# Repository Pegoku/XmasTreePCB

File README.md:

# XmasTreePCB

## Overview
This is a simple and customizable RGB Xmas tree.

## Features
- [x] **ESP32 Controlled**: Easy to program MCU.
- [x] **Neopixels**: Easy to use RGB LEDs.

## Media
<details>
    <summary>Images</summary>

)
</details>

<details>
    <summary>Video</summary>

</details>

## Contributing
Contributions are welcome! Please fork the repository and submit a pull request with your changes.

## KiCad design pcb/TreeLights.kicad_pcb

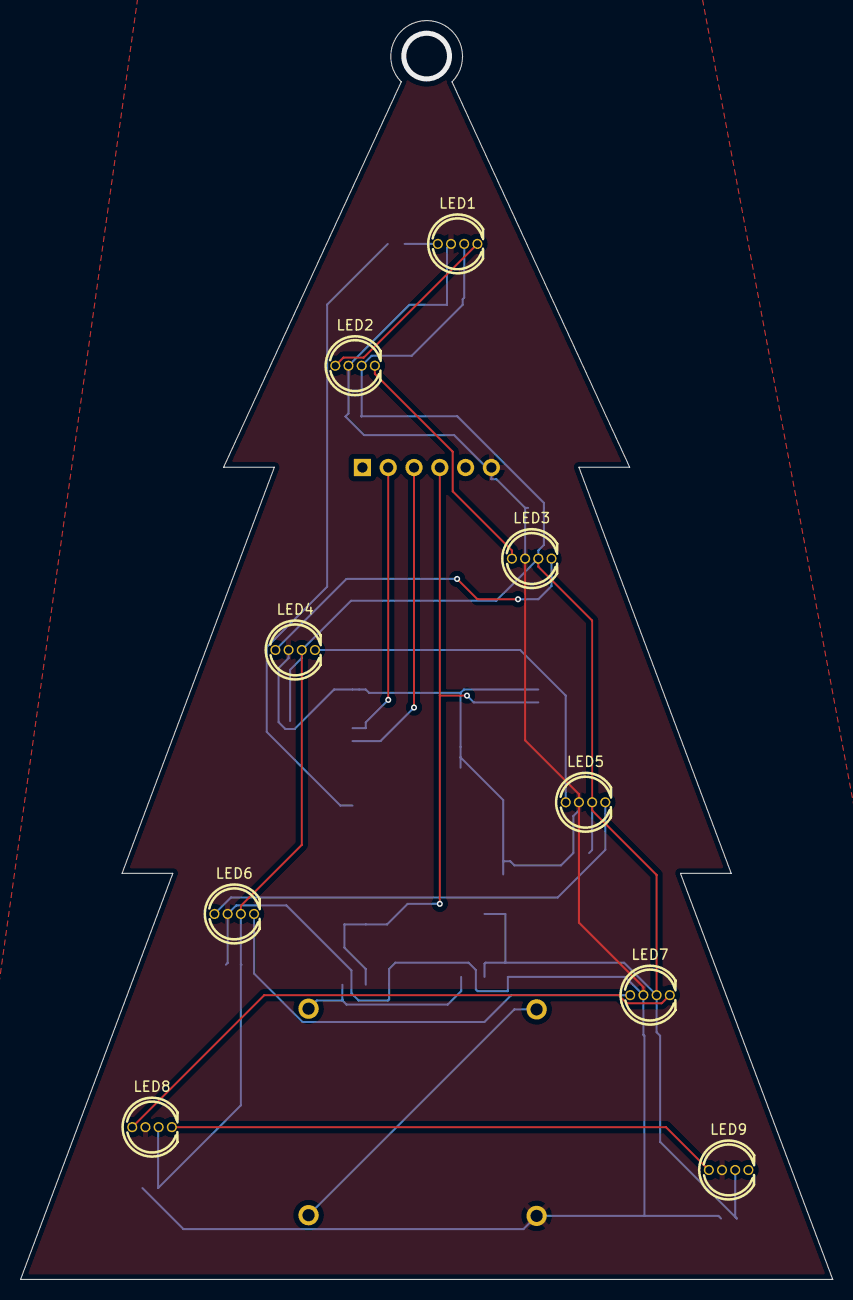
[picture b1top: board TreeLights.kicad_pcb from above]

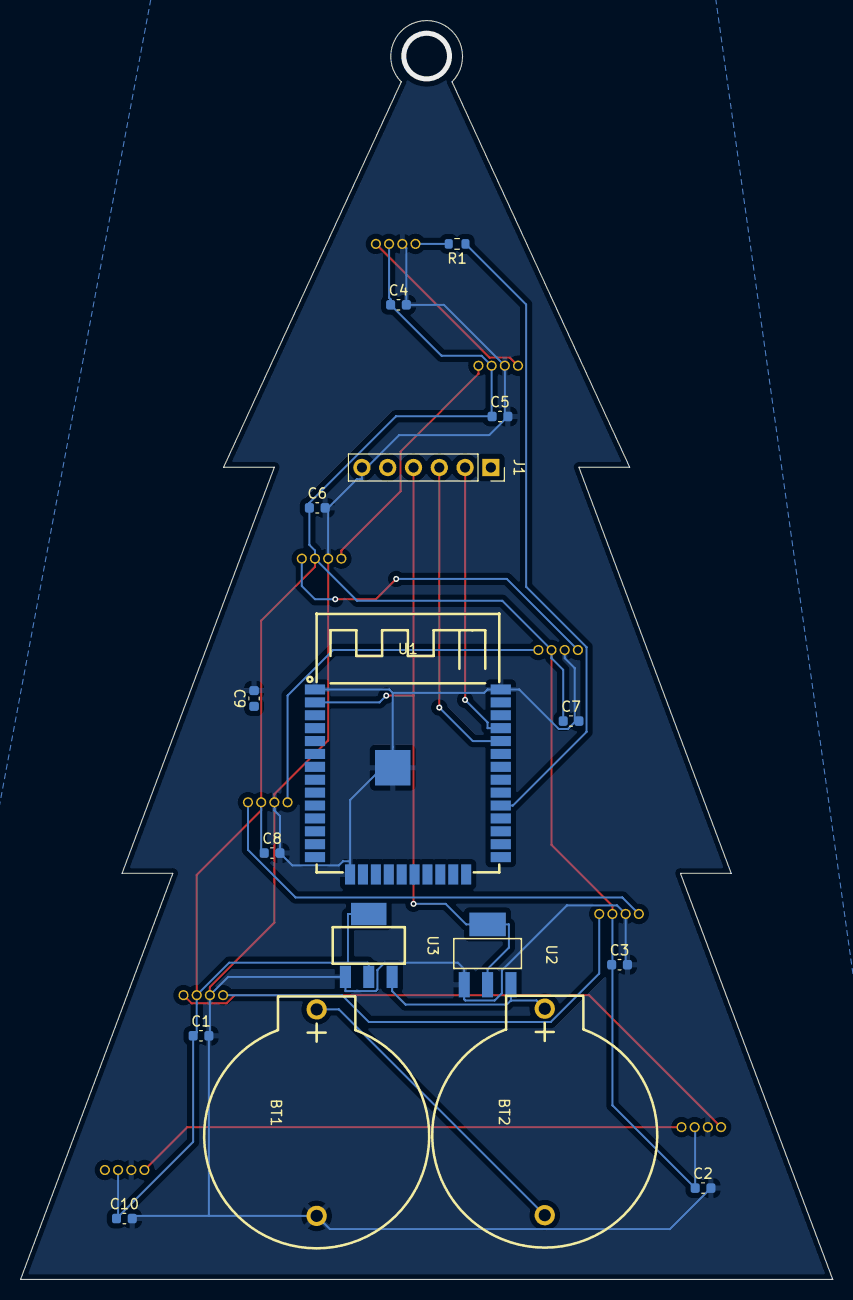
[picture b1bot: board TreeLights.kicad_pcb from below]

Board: 2 copper layers, 80.0 x 124.0 mm, 26 parts (17 on the bottom side), 17 nets.

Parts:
BT1, BT2: BS-02-A1AK006; BAT-TH_BS-02-A1AK006
C1, C2, C3, C4, C5, C6, C7, C8, C9, C10: 10uF; C_0603_1608Metric
J1: Conn_01x06; PinSocket_1x06_P2.54mm_Vertical
LED1, LED2, LED3, LED4, LED5, LED6, LED7, LED8, LED9: WS2812D-F5; LED-TH_4P-BD5.8-P1.30
R1: 300; R_0603_1608Metric
U1: ESP-WROOM-32E; COMM-SMD_ESP-WROOM-32D
U2: AZ1117H-3.3TRG1; SOT-223-3_L6.5-W3.4-P2.30-LS7.0-BR
U3: AMS1117-5.0_C347223; SOT-223_L6.7-W3.5-P2.30-BR

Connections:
+3.3V: C9.1, J1.4, U1.2 (3V3), U2.2 (OUTPUT), U2.4 (OUTPUT)
+5V: C1.1, C2.1, C3.1, C4.1, C5.1, C6.1, C7.1, C8.1, C10.1, LED1.2 (VDD), LED2.2 (VDD), LED3.2 (VDD), LED4.2 (VDD), LED5.2 (VDD), LED6.2 (VDD), LED7.2 (VDD), LED8.2 (VDD), LED9.2 (VDD), U3.2 (VOUT(TAB)), U3.4 (TAB)
+BATT: BT2.1, U2.3 (INPUT), U3.3 (VIN)
GND: BT1.2, C1.2, C2.2, C3.2, C4.2, C5.2, C6.2, C7.2, C8.2, C9.2, C10.2, J1.6, LED1.3 (GND), LED2.3 (GND), LED3.3 (GND), LED4.3 (GND), LED5.3 (GND), LED6.3 (GND), LED7.3 (GND), LED8.3 (GND), LED9.3 (GND), U1.1 (GND), U1.15 (GND), U1.38 (GND), U1.39 (P_GND), U2.1 (ADJ/GND), U3.1 (ADJ(GND))
unnamed: BT1.1, BT2.2
unnamed: J1.2, U1.35 (TXD0)
unnamed: J1.3, U1.34 (RXD0)
unnamed: LED1.4 (Din), R1.2
unnamed: LED1.1 (Dout), LED2.4 (Din)
unnamed: LED2.1 (Dout), LED3.4 (Din)
unnamed: LED3.1 (Dout), LED4.4 (Din)
unnamed: LED4.1 (Dout), LED5.4 (Din)
unnamed: LED5.1 (Dout), LED6.4 (Din)
unnamed: LED6.1 (Dout), LED7.4 (Din)
unnamed: LED7.1 (Dout), LED8.4 (Din)
unnamed: LED8.1 (Dout), LED9.4 (Din)
unnamed: R1.1, U1.29 (IO5)

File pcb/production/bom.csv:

Designator,Footprint,Quantity,Value,LCSC Part #
"BT1, BT2",BAT-TH_BS-02-A1AK006,2,BS-02-A1AK006,C964746
"C1, C10, C2, C3, C4, C5, C6, C7, C8, C9",0603,10,10uF,C19702
J1,PinSocket_1x06_P2.54mm_Vertical,1,Conn_01x06,
"LED1, LED2, LED3, LED4, LED5, LED6, LED7, LED8, LED9",LED-TH_4P-BD5.8-P1.30,9,WS2812D-F5,C190565
R1,0603,1,300,C114617
U1,COMM-SMD_ESP-WROOM-32D,1,ESP-WROOM-32E,C19949066
U2,SOT-223-3_L6.5-W3.4-P2.30-LS7.0-BR,1,AZ1117H-3.3TRG1,C110474
U3,SOT-223_L6.7-W3.5-P2.30-BR,1,AMS1117-5.0_C347223,C347223

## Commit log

2024-12-13 finish
